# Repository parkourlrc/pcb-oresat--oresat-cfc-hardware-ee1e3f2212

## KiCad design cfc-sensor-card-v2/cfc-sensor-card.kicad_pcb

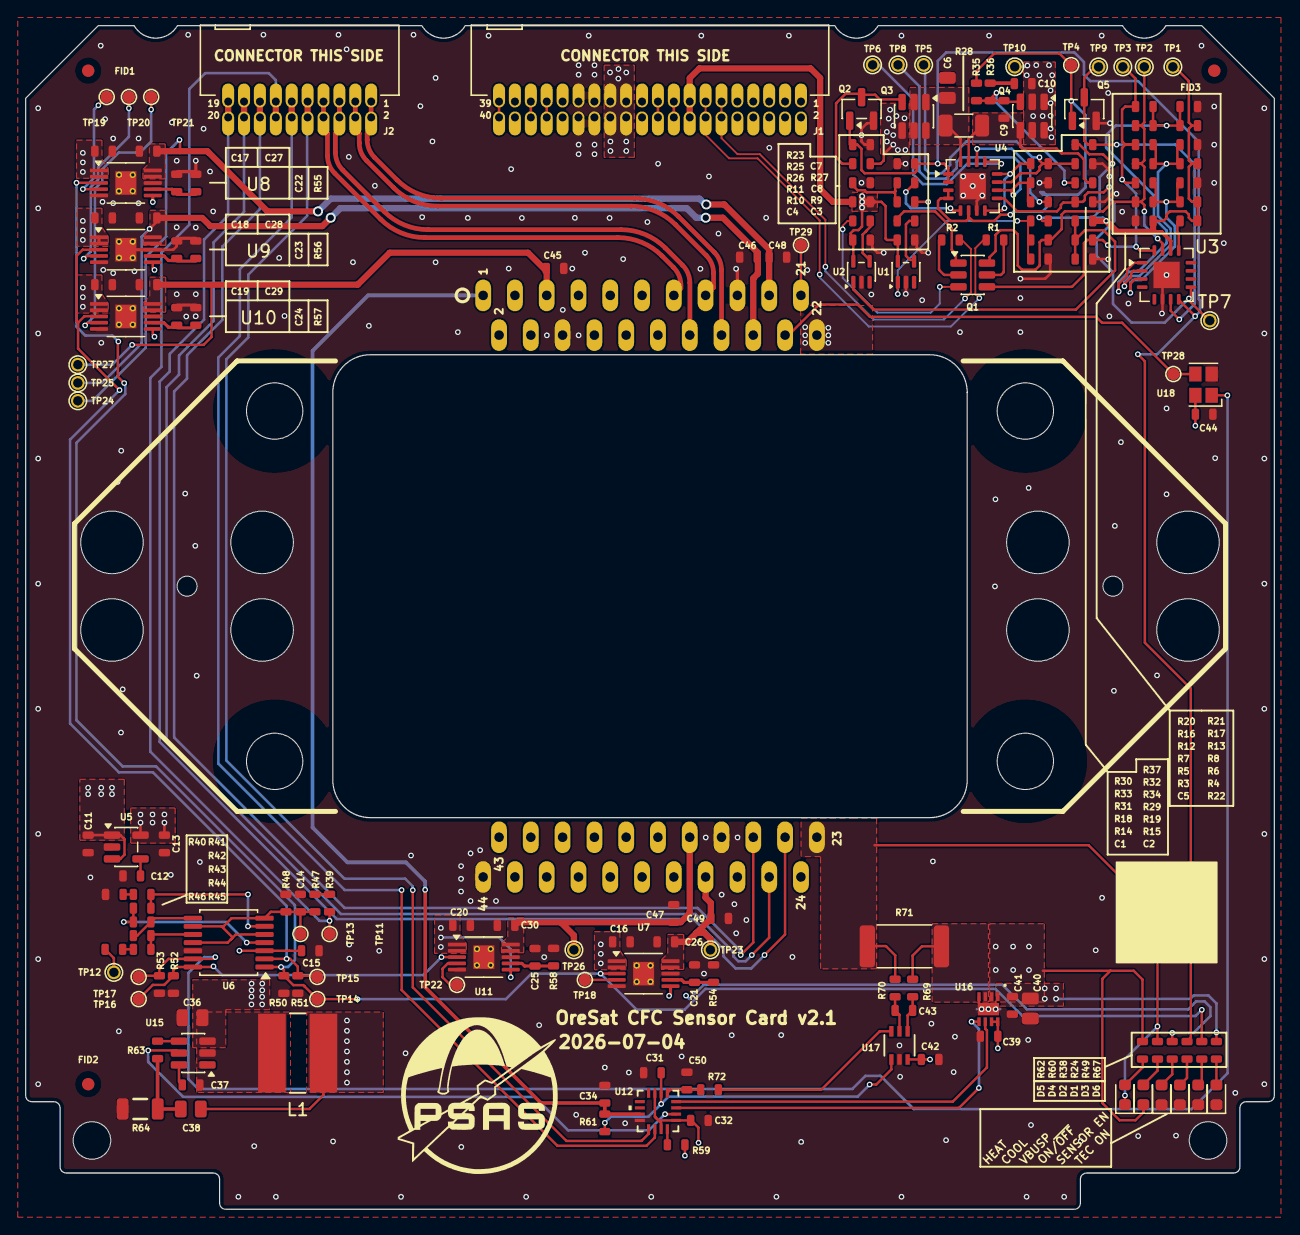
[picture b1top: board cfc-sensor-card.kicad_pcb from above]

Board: 4 copper layers, 99.8 x 94.6 mm, 181 parts (1 on the bottom side), 107 nets.

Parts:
C1, C2, C7, C8, C11, C14, C15: 1u; 0603-C-NOSILK
C3, C4, C5, C12, C31, C32, C34, C39, C41, C42, C44, C45, C46, C47, C48, C49, C50: 100n; 0603-C-NOSILK
C6, C36, C38, C40: 10u; 0805-C-NOSILK
C9, C37: 10n; 0603-C-NOSILK
C10, C21, C22, C23, C24, C25: 470n; 0603-C-NOSILK
C13, C16, C17, C18, C19, C20, C26, C27, C28, C29, C30: 4.7u; 0603-C-NOSILK
C43: .022uF; 0603-C-NOSILK
D1: AMB; LED_0603_1608Metric
D2, D3, D4, D6: GREEN; LED_0603_1608Metric
D5: AMBER; LED_0603_1608Metric
FID1, FID2, FID3: Fiducial; Fiducial_1mm_Mask2mm
J1: TFM-120-01-L-D-RA; J-SAMTEC-TFM-120-X1-XXX-D-RA
J2: J-SAMTEC-TFM-110-X1-XXX-D-RA
L1: 2.6u; Ind 2.6u 2A
PCB1: ORESAT-CARD-V1.3-CFC-SENSOR-V1.0
Q1: DMP2110UVTQ-7; SOT-23-6
Q2, Q5: DMN2050LQ-7; SOT-23
Q3: DMP3050LVT-7; TSOT-23-6
Q4: DMPH2040UVTQ-7; TSOT-23-6
R1, R2, R4, R8, R11, R21, R30, R31, R69, R70, R72: 100; 0603-C-NOSILK
R3, R5, R6, R7, R12, R13, R16, R17, R20: NP; 0603-C-NOSILK
R9, R10: 665K; 0603-C-NOSILK
R14, R15, R48: 330K; 0603-C-NOSILK
R18, R19: 1M; 0603-C-NOSILK
R22, R23, R25, R29, R34, R37, R38, R39, R40, R41, R42, R43, R44, R45, R46, R47, R49, R50, R51, R52, R53, R59, R60, R61, R67: 10K; 0603-C-NOSILK
R24, R62: 4.7K; 0603-C-NOSILK
R26: 100k; 0603-C-NOSILK
R27, R35, R36: 10k; 0603-C-NOSILK
R28: 10m; R_1206_3216Metric
R32, R33, R63: 1k; 0603-C-NOSILK
R54, R55: 33.2K; 0603-C-NOSILK
R56: 16.2K; 0603-C-NOSILK
R57: 9.09K; 0603-C-NOSILK
R58: 29.4K; 0603-C-NOSILK
R64: 50m; 1206-C
R71: 15m; R_2512_6332Metric
TP1, TP9, TP10, TP12, TP23, TP24, TP25, TP26, TP27: Test-Point; TestPoint-0.75mm-th
TP2, TP3, TP5, TP6, TP7, TP8: TEST-POINT; TestPoint-0.75mm-th
TP4, TP11, TP13, TP14, TP15, TP16, TP17, TP18, TP19, TP20, TP21, TP22, TP28, TP29: TestPoint-MinTH; TestPoint_Pad_D1.0mm
U1, U2: MIC842LYC5; SOT-353_SC-70-5
U3: MAX7310ATE+; QFN-16-1EP_4x4mm_P0.65mm_EP2.1x2.1mm
U4: MAX4211FETE; QFN-16-1EP_4x4mm_P0.65mm_EP2.1x2.1mm
U5: LP2985-3.3; SOT-23-5
U6: TLC3704IPWR; TSSOP-14_4.4x5mm_P0.65mm
U7, U8, U9, U10, U11: LT3042IMSE; MSOP-10-1EP_3x3mm_P0.5mm_EP1.68x1.88mm_0.254_ThermalVias
U12: AD5593RBCPZ-RL7; 16-WFQFN, CSP
U15: MP2410A; TSOT-23-6
U16: DRV8212DSGR; WSON_212DSGR_TEX
U17: INA186A1IDCKR; SOIC_IDCKR_TEX
U18: XO_ISM95-XXXXXX
U19: U-PIRT-PIRT1280A1-12; PIRT1280A1-12

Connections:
2.5VREF: C31.1, R61.1, U12.6 (VREF), U17.1 (REF)
3.3V: C13.1, C15.1, C32.1, C39.1, C42.1, C44.1, R46.2, R59.1, TP12.1 (1_1), U5.5 (VOUT), U6.3 (VDD), U12.1 (VDD), U12.7 (VLOGIC), U12.15 (~RESET), U16.7 (MODE), U16.8 (VCC), U17.3 (VS), U18.4 (VCC)
/CAN1_H: J1.33, J1.34
/CAN1_L: J1.35, J1.36
/CAN2_H: J1.17, J1.18
/CAN2_L: J1.19, J1.20
/I2C1_CLK: J2.11, J2.12, U12.14 (SCL)
/I2C1_SDA: J2.9, J2.10, U12.13 (SDA)
/OPD/AD0: R16.2, R17.1, R20.2, R21.1, U3.1 (AD0)
/OPD/AD1: R7.2, R8.1, R12.2, R13.1, U3.2 (AD1)
/OPD/AD2: R3.2, R4.1, R5.2, R6.1, U3.3 (AD2)
/OPD/CB-RESET: R29.2, TP7.1 (1_1), U3.9 (IO4), U4.9 (CIN2-)
/OPD/CB_CTRL: Q5.1 (G), R35.2, TP4.1 (1_1), U4.3 (LE), U4.4 (COUT1), U4.6 (COUT2)
/OPD/IOUT: R31.1, U4.14 (IOUT)
/OPD/ON/~OFF: C7.2, Q2.1 (G), R23.2, R24.1, U3.8 (IO3), U4.1 (VCC), U4.2 (IN)
/OPD/OPD_PWR: J1.15, J1.16, R11.1
/OPD/OPD_SCL: J1.13, J1.14, R1.1
/OPD/OPD_SDA: J1.11, J1.12, R2.1
/OPD/PEN-SCL-FILT: Q1.6 (D), R3.1, R7.1, R14.2, R16.1, TP2.1 (1_1), U3.15 (SCL)
/OPD/PEN-SDA-FILT: Q1.4 (D), R5.1, R12.1, R15.2, R20.1, TP3.1 (1_1), U3.16 (SDA)
/OPD/POUT: TP6.1 (1_1), U4.13 (POUT)
/OPD/~FAULT: Q5.3 (D), R37.1, TP9.1 (1_1), U3.7 (IO2)
/OUT1_N: J2.5, J2.6, U19.14 (OUT1N)
/OUT1_P: J2.7, J2.8, U19.13 (OUT1P)
/PIRT/CLK_EN: R53.1, TP17.1 (1_1), U6.13 (4OUT), U18.1 (INH)
/PIRT/TEC+: D5.1 (K), R60.2, R70.2, R71.2, U19.23 (TEC+)
/PIRT/TEC-: D4.1 (K), R62.1, U16.2 (OUT1), U19.22 (TEC-)
/PIRT/THERM+: C34.1, R61.2, U12.11 (I/O7), U19.1 (THERM+)
/SENSOR_ENABLE: J2.13, J2.14, R39.1, TP11.1 (1_1)
/SPI_CLK: J2.17, J2.18, U19.26 (SDCLK)
/SPI_MISO: J2.15, J2.16, U19.27 (SDOUT)
/SPI_MOSI: J2.19, J2.20, U19.25 (SDIN)
/TEC Control/BRIDGE_DIR: U12.4 (I/O2), U16.6 (IN1/PH)
/TEC Control/BRIDGE_EN: U12.3 (I/O1), U16.5 (IN2/EN)
/TEC Control/CURRENT_SET: U12.2 (I/O0), U15.5 (EN/DIM)
/TEC Control/TEC_SENSE: C50.1, R72.1, U12.5 (I/O3)
/TXCLK_N: J2.1, J2.2, U19.16 (TXCLKN)
/TXCLK_P: J2.3, J2.4, U19.15 (TXCLKP)
/~SD: J1.39, J1.40
GND: C1.1, C2.1, C3.1, C4.1, C5.2, C6.1, C7.1, C11.2, C12.2, C13.2, C14.2, C15.2, C16.2, C17.2, C18.2, C19.2, C20.2, C21.2, C22.2, C23.2, C24.2, C25.2, C26.2, C27.2, C28.2, C29.2, C30.2, C31.2, C32.2, C34.2, C36.2, C39.2, C40.2, C41.2, C42.2, C44.2, C45.2, C46.2, C47.2, C48.2, C49.2, C50.2, D1.1 (K), D2.1 (K), D3.1 (K), D6.1 (K), J1.27, J1.28, J1.29, J1.30, Q2.2 (S), Q5.2 (S), R6.2, R13.2, R21.2, R23.1, R26.1, R29.1, R32.1, R33.1, R40.1, R48.1, R50.2, R51.2, R52.2, R53.2, R54.2, R55.2, R56.2, R57.2, R58.2, R64.2, U1.2 (GND), U2.2 (GND), U3.6 (GND), U3.17 (GND), U4.7 (GND), U4.17 (GND), U5.2 (GND), U6.12 (GND), U7.5 (ILIM), U7.8 (GND), U7.11 (GND), U8.5 (ILIM), U8.8 (GND), U8.11 (GND), U9.5 (ILIM), U9.8 (GND), U9.11 (GND), U10.5 (ILIM), U10.8 (GND), U10.11 (GND), U11.5 (ILIM), U11.8 (GND), U11.11 (GND), U12.12 (GND), U15.1 (GND), U16.4 (GND), U16.9 (GND), U17.2 (GND), U18.2 (GND), U19.6 (VNOUT), U19.17 (VN), U19.29 (VGND), U19.44 (THERM-)
unnamed: C8.1, R26.2, R27.2
unnamed: C10.2, R36.2
unnamed: C38.2, R63.2, R64.1
unnamed: D1.2 (A), R24.2
unnamed: D2.2 (A), R38.1
unnamed: D3.2 (A), R49.2
unnamed: D4.2 (A), R60.1
unnamed: D5.2 (A), R62.2
unnamed: D6.2 (A), R67.1
unnamed: Q1.1 (G), R9.2
unnamed: Q1.5 (S), R1.2
unnamed: Q1.3 (G), R10.2
unnamed: Q1.2 (S), R2.2
unnamed: Q2.3 (D), Q3.3 (G), R25.1
unnamed: C9.2, Q4.3 (G), R34.1, R35.1, R36.1
unnamed: C9.1, Q4.4 (S), R28.2, R34.2, U4.15 (RS-)
unnamed: R39.2, R47.1
unnamed: R40.2, R41.1
unnamed: R45.2, R46.1
unnamed: C1.2, R14.1, R18.1, U1.1 (INP)
unnamed: R9.1, U1.4 (OUT)
unnamed: C2.2, R15.1, R19.1, U2.1 (INP)
unnamed: R10.1, U2.4 (OUT)
unnamed: R22.2, U3.13 (~RESET)
unnamed: R31.2, R33.2, TP8.1 (1_1), U4.10 (CIN1+)
unnamed: R30.2, R32.2, TP5.1 (1_1), U4.11 (CIN1-)
unnamed: R30.1, U4.8 (CIN2+), U4.12 (REF)
unnamed: R27.1, U4.5 (INHIBIT)
unnamed: C6.2, Q3.1 (D), Q3.2 (D), Q3.5 (D), Q3.6 (D), R28.1, U4.16 (RS+)
unnamed: C12.1, U5.4 (BP)
unnamed: C14.1, R47.2, R48.2, TP13.1 (1_1), U6.5 (2IN+), U6.7 (1IN+), U6.9 (3IN+), U6.11 (4IN+)
unnamed: R41.2, R42.1, U6.6 (1IN-)
unnamed: R49.1, R50.1, TP14.1 (1_1), U6.1 (1OUT), U7.3 (EN/UV), U8.3 (EN/UV)
unnamed: R42.2, R43.1, U6.4 (2IN-)
unnamed: R43.2, R44.1, U6.8 (3IN-)
unnamed: R44.2, R45.1, U6.10 (4IN-)
unnamed: TP18.1 (1_1), U7.4 (PG)
unnamed: C21.1, R54.1, U7.7 (SET)
unnamed: TP19.1 (1_1), U8.4 (PG)
unnamed: C22.1, R55.1, U8.7 (SET)
unnamed: TP20.1 (1_1), U9.4 (PG)
unnamed: C23.1, R56.1, U9.7 (SET)
unnamed: R51.1, TP15.1 (1_1), U6.2 (2OUT), U9.3 (EN/UV), U10.3 (EN/UV)
unnamed: TP21.1 (1_1), U10.4 (PG)
unnamed: C24.1, R57.1, U10.7 (SET)
unnamed: R52.1, TP16.1 (1_1), U6.14 (3OUT), U11.3 (EN/UV)
unnamed: TP22.1 (1_1), U11.4 (PG)
unnamed: C25.1, R58.1, U11.7 (SET)
unnamed: R59.2, U12.16 (A0)
unnamed: C37.1, U15.6 (BST)
unnamed: R63.1, U15.4 (FB)
unnamed: C37.2, L1.1, U15.2 (SW)
unnamed: R69.2, R71.1, U16.3 (OUT2)
unnamed: C38.1, C40.1, C41.1, L1.2, R67.2, U16.1 (VM)
unnamed: C43.1, R69.1, U17.4 (IN+)
unnamed: C43.2, R70.1, U17.5 (IN-)
unnamed: R72.2, U17.6 (OUT)
unnamed: TP28.1 (1_1), U18.3 (CLK), U19.20 (REFCLK)
unnamed: TP29.1 (1_1), U19.21 (JAMSYNC)
VBUS: J1.23, J1.24, J1.25, J1.26, Q3.4 (S), R25.2
VBUSP: C8.2, C10.1, C11.1, C16.1, C17.1, C18.1, C19.1, C20.1, C36.1, Q4.1 (D), Q4.2 (D), Q4.5 (D), Q4.6 (D), R38.2, TP10.1 (1_1), U5.1 (VIN), U5.3 (ON/~OFF), U7.1 (IN), U7.2 (IN), U7.6 (PGFB), U8.1 (IN), U8.2 (IN), U8.6 (PGFB), U9.1 (IN), U9.2 (IN), U9.6 (PGFB), U10.1 (IN), U10.2 (IN), U10.6 (PGFB), U11.1 (IN), U11.2 (IN), U11.6 (PGFB), U15.3 (VIN)
VDETCOM-2.9V: C30.1, C47.1, TP26.1 (1_1), U11.9 (OUTS), U11.10 (OUT), U19.31 (VDETCOM-2.9V)
VPD: C3.2, C4.2, C5.1, R4.2, R8.2, R11.2, R17.2, R18.2, R19.2, R22.1, R37.2, TP1.1 (1_1), U1.5 (VDD), U2.5 (VDD), U3.14 (V+)
VPH-3.3V: C27.1, C48.1, TP24.1 (1_1), U8.9 (OUTS), U8.10 (OUT), U19.19 (VPH-3.3V)
VPL-1.6V: C28.1, C46.1, TP25.1 (1_1), U9.9 (OUTS), U9.10 (OUT), U19.18 (VPL-1.6V)
VPOS-3.3V: C26.1, C49.1, TP23.1 (1_1), U7.9 (OUTS), U7.10 (OUT), U19.30 (VPOS-3.3V)
VPOUT-0.9V: C29.1, C45.1, TP27.1 (1_1), U10.9 (OUTS), U10.10 (OUT), U19.5 (VPOUT-0.9V)
